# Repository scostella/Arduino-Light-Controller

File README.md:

# Arduino Light Controller

The **Arduino Light Controller** is a passive output board designed to provide simple, reliable **on/off control of up to 16 lighting channels** using an Arduino microcontroller. The board routes Arduino I/O pins directly to lighting outputs and includes optional onboard current‑limiting resistors for direct LED connection.

This controller is intended for use with the **Arduino CMRI Library** in conjunction with an associated CMRI‑compatible shield.

---

## Overview

The Arduino Light Controller connects Arduino digital or analog output pins to low‑current lighting loads. Each output is strictly **on or off**—there is no dimming, PWM, or active drive circuitry on the board.

The design emphasizes:

- Electrical simplicity  
- Clear signal routing  
- Safe use within Arduino current limits  
- Compatibility with Arduino CMRI‑based control systems  

---

## Key Characteristics

- 16 independent lighting output channels  
- On/off control only  
- Arduino 5 V I/O pins directly power outputs  
- Optional onboard 1 kΩ series resistors for LEDs  
- Jumper‑selectable resistor bypass per channel  
- Designed for Arduino CMRI Library usage with a compatible shield  
- Passive design (no relays, MOSFETs, or drivers)  

---

## Assembled Board

The image above shows the assembled Arduino Light Controller PCB with all connectors and headers populated.

---

## Board Layout and Function

### Top of Board – Arduino Control Headers

At the **top edge of the board** is a row of **four 4‑pin headers**.

- These headers connect directly to **Arduino digital or analog output pins**
- Together they control **16 lighting channels**
- Each pin corresponds to **one lighting output**
- Typically connected via ribbon cable or directly from a CMRI‑compatible shield

Each Arduino output pin switches one lighting channel on or off.

---

### Middle of Board – Resistor Bypass Headers

In the **center of the board** are **two rows of eight 2‑pin headers**.

- Each header corresponds to **one lighting channel**
- These headers allow bypassing the onboard **1 kΩ series resistor**

#### Built‑In Current Limiting

- Each output includes a **1 kΩ resistor** in series
- This allows **LEDs to be connected directly** to the board without external resistors

#### Resistor Bypass

- If the connected lighting already includes its own resistance:
  - A jumper may be installed on the corresponding 2‑pin header
  - This **bypasses the onboard 1 kΩ resistor**

This provides flexibility for:
- Pre‑resisted LEDs  
- Commercial lighting assemblies  
- External resistor networks  

---

### Bottom of Board – Light Output Headers

At the **bottom edge of the board** is a row of **sixteen 2‑pin headers**.

- Each header corresponds directly to one Arduino control pin
- Used to connect the lighting loads

#### Output Polarity

- **Top pin:** Positive (Arduino output)  
- **Bottom pin:** Ground / Negative  

⚠️ **Important:**  
Lighting loads are powered **directly from Arduino I/O pins**.  
Do not exceed Arduino per‑pin or total I/O current limits.

---

### Power Bus and Daisy Chaining

As with other modules in this series, the board includes:

- One **3‑pin header in the top‑left corner**
- One **3‑pin header in the top‑right corner**

These headers provide a shared **power bus** for:

- **12 V**
- **5 V**
- **Ground**

#### Power Bus Notes

- Allows **daisy chaining multiple modules**
- Maximum combined current across the bus: **3 A**
- Intended for system power distribution only  
  (lighting outputs are not powered from this bus)

---

## Electrical Characteristics and Limitations

- Control type: **On/Off only**
- No dimming or PWM
- No active output drivers
- No isolation from Arduino I/O
- Outputs driven directly from Arduino pins
- Designed for low‑current lighting only

⚠️ **Exceeding Arduino current limits may damage the microcontroller.**

---

## Intended Use

This board is well suited for:

- Arduino CMRI‑based layouts
- Model railroad lighting and structures
- Control panels and indicators
- Building and interior lighting
- Any application requiring simple, predictable lighting control

---

## Limited Liability and Disclaimer

This project is provided as an **open‑source hardware design** and is offered **as‑is**, without warranty of any kind.

By using this design, documentation, or any assembled hardware provided by the author, you agree to the following:

- You assume **all responsibility** for proper electrical design, wiring, installation, and use
- The author makes **no guarantees** regarding suitability for any specific application
- The author shall not be held liable for:
  - Damage to equipment
  - Electrical failures
  - Personal injury
  - Property damage
  - Losses resulting from improper use, installation, or modification

Use of this project or any associated hardware constitutes acceptance of these terms.

---

## Availability and Purchase

Fully **assembled and tested** Arduino Light Controller boards are available.

- **Price:** $35 USD per board  
- **Shipping:** Additional, based on destination  
- **Contact:**  
  📧 scostella@seancostella.com  

Please contact the author for current availability, lead times, and shipping details.

---

## Reference Projects

This project integrates with the Arduino CMRI ecosystem. The following projects provide related hardware, firmware, and configuration support:

- **Arduino Mega CMRI WiFi**  
  Arduino sketch for Mega 2560 to operate as CMRI Node with an ESP8266-ESP01 providing WiFi connectivity.
  https://github.com/scostella/Arduino_Mega_CMRI_WiFi

- **ESP8266 WiFi Setup Utility**  
  ESP sketch to program the ESP8266-ESP01 to work with the Arduino Mega 2560 and connection configuration for your WiFi network.
  https://github.com/scostella/ESP8266WiFiSetup
  
- **KiCad Custom Library**  
  Library containing all project parts in all designs.
  https://github.com/scostella/KiCadLibrary

- **Arduino Mega CMRI WiFi Shield**  
  KiCad design for a shield for the Arduino Mega 2560 facilitating easy integration with the ESP8266-ESP01 and the CMRI modules listed below.
  https://github.com/scostella/Arduino_Mega_CMRI_WiFi_Shield

- **Arduino Accessory Controller**  
  KiCad design for a board to control accessories up to 1 amp.
  https://github.com/scostella/Arduino-Accessory-Controller

- **Arduino IR Sensor Module - 8 Port**  
  KiCad design for a board to use TCRT5000 IR module to sense object presence which can also be used in the Arduino Mega CMRI WiFi module to group sensors to create virtual block detection.
  https://github.com/scostella/Arduino_IR_Sensor_Module_-_8_Port

- **Arduino Tortoise Controller with Feedback - 8 Port**  
  KiCad design for a board to control Circuitron Tortoise Slow Motion Switch machines and provide feedback on switch position either controlled internally by the voltage applied to the tortoise or an external signal.
  https://github.com/scostella/Arduino_Tortoise_Controller_with_Feedback_-_8_Port

- **Arduino Light Controller**  
  KiCad design for a board to control low amperage lighting and other loads (<10ma) using the Arduino's 5V source.
  https://github.com/scostella/Arduino-Light-Controller

These projects may be used together to form a complete CMRI‑controlled lighting and I/O system.

---

## Repository Contents

```text
/
├── Arduino Light Controller.kicad_pcb        # KiCad PCB Layout
├── Arduino Light Controller.kicad_prl        # KiCad Project Settings
├── Arduino Light Controller.kicad_pro        # KiCad Project
├── Arduino Light Controller.kicad_sch        # KiCad Schematics
├── PowerLED.kicad_sch                        # KiCad Power and LED module
├── ResistorNet.kicad_sch                     # KiCad Light Control Resistor and Bypass module
├── Arduino Light Controller.jpg              # Board Rendering
└── README.md

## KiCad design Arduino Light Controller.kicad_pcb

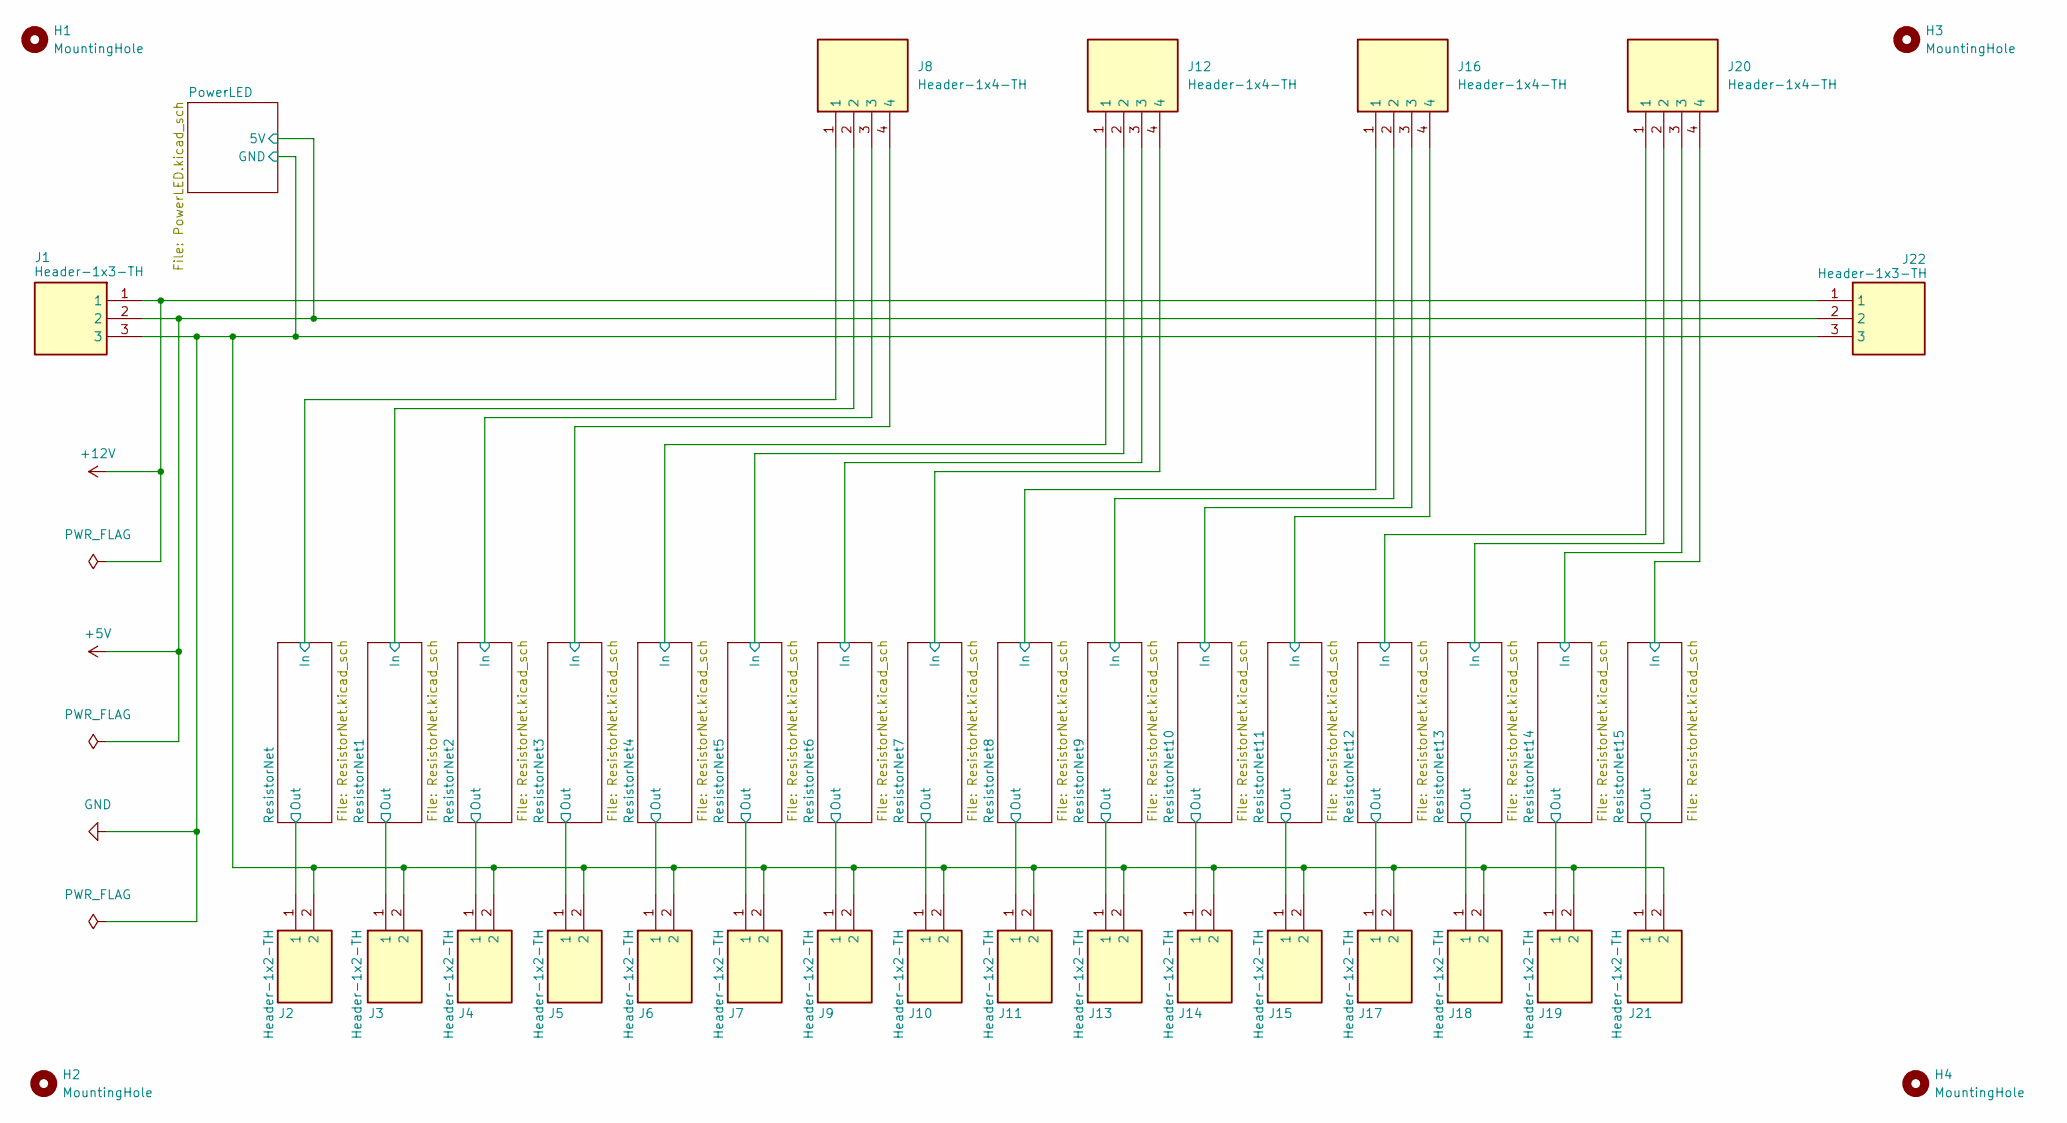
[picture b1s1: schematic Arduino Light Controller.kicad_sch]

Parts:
H1, H2, H3, H4: MountingHole; MountingHole_3.2mm_M3_ISO7380
J1, J22: Header-1x3-TH; 710-61300311121; Mouser Part Number 710-61300311121
J2, J3, J4, J5, J6, J7, J9, J10, J11, J13, J14, J15, J17, J18, J19, J21: Header-1x2-TH; 710-61300211121; Mouser Part Number 710-61300211121
J8, J12, J16, J20: Header-1x4-TH; 710-61300411121; Mouser Part Number 710-61300411121

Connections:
+5V: J1.2, J22.2; also elsewhere on the board
+12V: J1.1, J22.1
/ResistorNet1/In: J8.2; also elsewhere on the board
/ResistorNet1/Out: J3.1; also elsewhere on the board
/ResistorNet2/In: J8.3; also elsewhere on the board
/ResistorNet2/Out: J4.1; also elsewhere on the board
/ResistorNet3/In: J8.4; also elsewhere on the board
/ResistorNet3/Out: J5.1; also elsewhere on the board
/ResistorNet4/In: J12.1; also elsewhere on the board
/ResistorNet4/Out: J6.1; also elsewhere on the board
/ResistorNet5/In: J12.2; also elsewhere on the board
/ResistorNet5/Out: J7.1; also elsewhere on the board
/ResistorNet6/In: J12.3; also elsewhere on the board
/ResistorNet6/Out: J9.1; also elsewhere on the board
/ResistorNet7/In: J12.4; also elsewhere on the board
/ResistorNet7/Out: J10.1; also elsewhere on the board
/ResistorNet8/In: J16.1; also elsewhere on the board
/ResistorNet8/Out: J11.1; also elsewhere on the board
/ResistorNet9/In: J16.2; also elsewhere on the board
/ResistorNet9/Out: J13.1; also elsewhere on the board
/ResistorNet10/In: J16.3; also elsewhere on the board
/ResistorNet10/Out: J14.1; also elsewhere on the board
/ResistorNet11/In: J16.4; also elsewhere on the board
/ResistorNet11/Out: J15.1; also elsewhere on the board
/ResistorNet12/In: J20.1; also elsewhere on the board
/ResistorNet12/Out: J17.1; also elsewhere on the board
/ResistorNet13/In: J20.2; also elsewhere on the board
/ResistorNet13/Out: J18.1; also elsewhere on the board
/ResistorNet14/In: J20.3; also elsewhere on the board
/ResistorNet14/Out: J19.1; also elsewhere on the board
/ResistorNet15/In: J20.4; also elsewhere on the board
/ResistorNet15/Out: J21.1; also elsewhere on the board
/ResistorNet/In: J8.1; also elsewhere on the board
/ResistorNet/Out: J2.1; also elsewhere on the board
GND: J1.3, J2.2, J3.2, J4.2, J5.2, J6.2, J7.2, J9.2, J10.2, J11.2, J13.2, J14.2, J15.2, J17.2, J18.2, J19.2, J21.2, J22.3; also elsewhere on the board

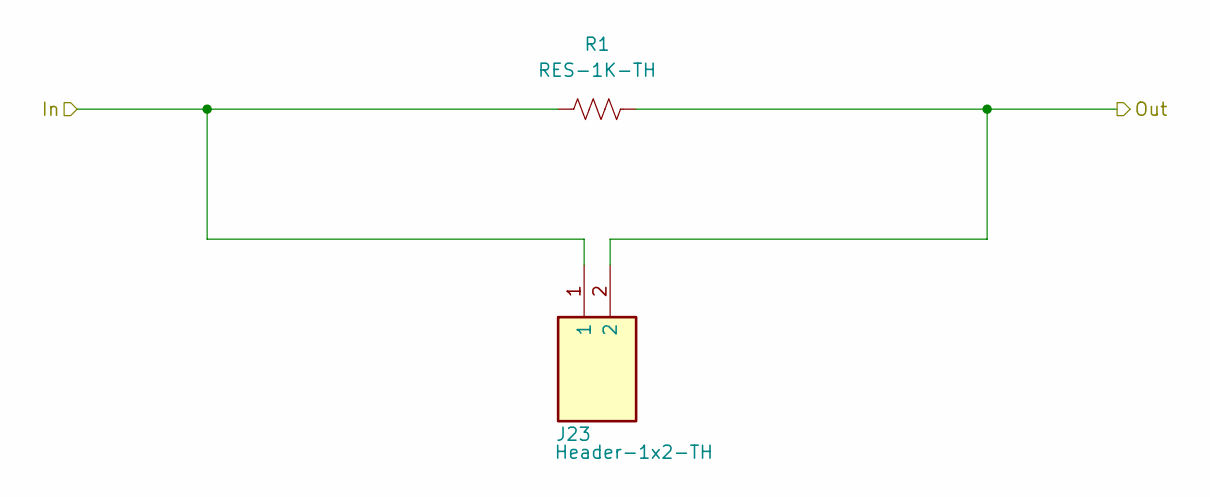
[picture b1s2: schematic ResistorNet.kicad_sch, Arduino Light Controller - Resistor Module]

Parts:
J23: Header-1x2-TH; 710-61300211121; Mouser Part Number 710-61300211121
R1: RES-1K-TH; R_Axial_DIN0204_L3.6mm_D1.6mm_P7.62mm_Horizontal; Mouser Part Number N/A

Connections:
/ResistorNet/In: J23.1, R1.1; also elsewhere on the board
/ResistorNet/Out: J23.2, R1.2; also elsewhere on the board

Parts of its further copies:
J24, J25, J26, J27, J28, J29, J30, J31, J32, J33, J34, J35, J36, J37, J38: Header-1x2-TH; 710-61300211121; Mouser Part Number 710-61300211121
R2, R3, R4, R5, R6, R7, R8, R9, R10, R11, R12, R13, R14, R15, R16: RES-1K-TH; R_Axial_DIN0204_L3.6mm_D1.6mm_P7.62mm_Horizontal; Mouser Part Number N/A

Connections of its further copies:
/ResistorNet1/In: J24.1, R2.1; also elsewhere on the board
/ResistorNet1/Out: J24.2, R2.2; also elsewhere on the board
/ResistorNet2/In: J25.1, R3.1; also elsewhere on the board
/ResistorNet2/Out: J25.2, R3.2; also elsewhere on the board
/ResistorNet3/In: J26.1, R4.1; also elsewhere on the board
/ResistorNet3/Out: J26.2, R4.2; also elsewhere on the board
/ResistorNet4/In: J27.1, R5.1; also elsewhere on the board
/ResistorNet4/Out: J27.2, R5.2; also elsewhere on the board
/ResistorNet5/In: J28.1, R6.1; also elsewhere on the board
/ResistorNet5/Out: J28.2, R6.2; also elsewhere on the board
/ResistorNet6/In: J29.1, R7.1; also elsewhere on the board
/ResistorNet6/Out: J29.2, R7.2; also elsewhere on the board
/ResistorNet7/In: J30.1, R8.1; also elsewhere on the board
/ResistorNet7/Out: J30.2, R8.2; also elsewhere on the board
/ResistorNet8/In: J31.1, R9.1; also elsewhere on the board
/ResistorNet8/Out: J31.2, R9.2; also elsewhere on the board
/ResistorNet9/In: J32.1, R10.1; also elsewhere on the board
/ResistorNet9/Out: J32.2, R10.2; also elsewhere on the board
/ResistorNet10/In: J33.1, R11.1; also elsewhere on the board
/ResistorNet10/Out: J33.2, R11.2; also elsewhere on the board
/ResistorNet11/In: J34.1, R12.1; also elsewhere on the board
/ResistorNet11/Out: J34.2, R12.2; also elsewhere on the board
/ResistorNet12/In: J35.1, R13.1; also elsewhere on the board
/ResistorNet12/Out: J35.2, R13.2; also elsewhere on the board
/ResistorNet13/In: J36.1, R14.1; also elsewhere on the board
/ResistorNet13/Out: J36.2, R14.2; also elsewhere on the board
/ResistorNet14/In: J37.1, R15.1; also elsewhere on the board
/ResistorNet14/Out: J37.2, R15.2; also elsewhere on the board
/ResistorNet15/In: J38.1, R16.1; also elsewhere on the board
/ResistorNet15/Out: J38.2, R16.2; also elsewhere on the board

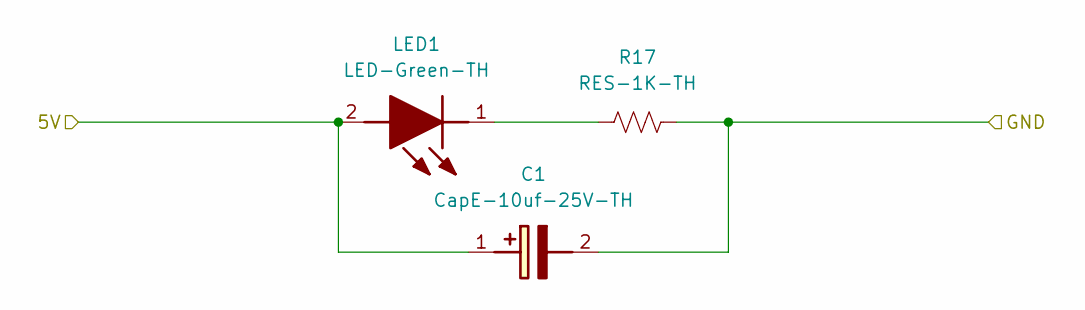
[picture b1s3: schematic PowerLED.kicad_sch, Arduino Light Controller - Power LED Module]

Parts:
C1: CapE-10uf-25V-TH; 710-860010472002; Mouser Part Number 710-860010472002
LED1: LED-Green-TH; 604-WP7113GD; Mouser Part Number 604-WP7113GD
R17: RES-1K-TH; R_Axial_DIN0204_L3.6mm_D1.6mm_P7.62mm_Horizontal; Mouser Part Number N/A

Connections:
+5V: C1.1 (+), LED1.2 (A); also elsewhere on the board
GND: C1.2 (-), R17.2; also elsewhere on the board
unnamed: LED1.1 (K), R17.1

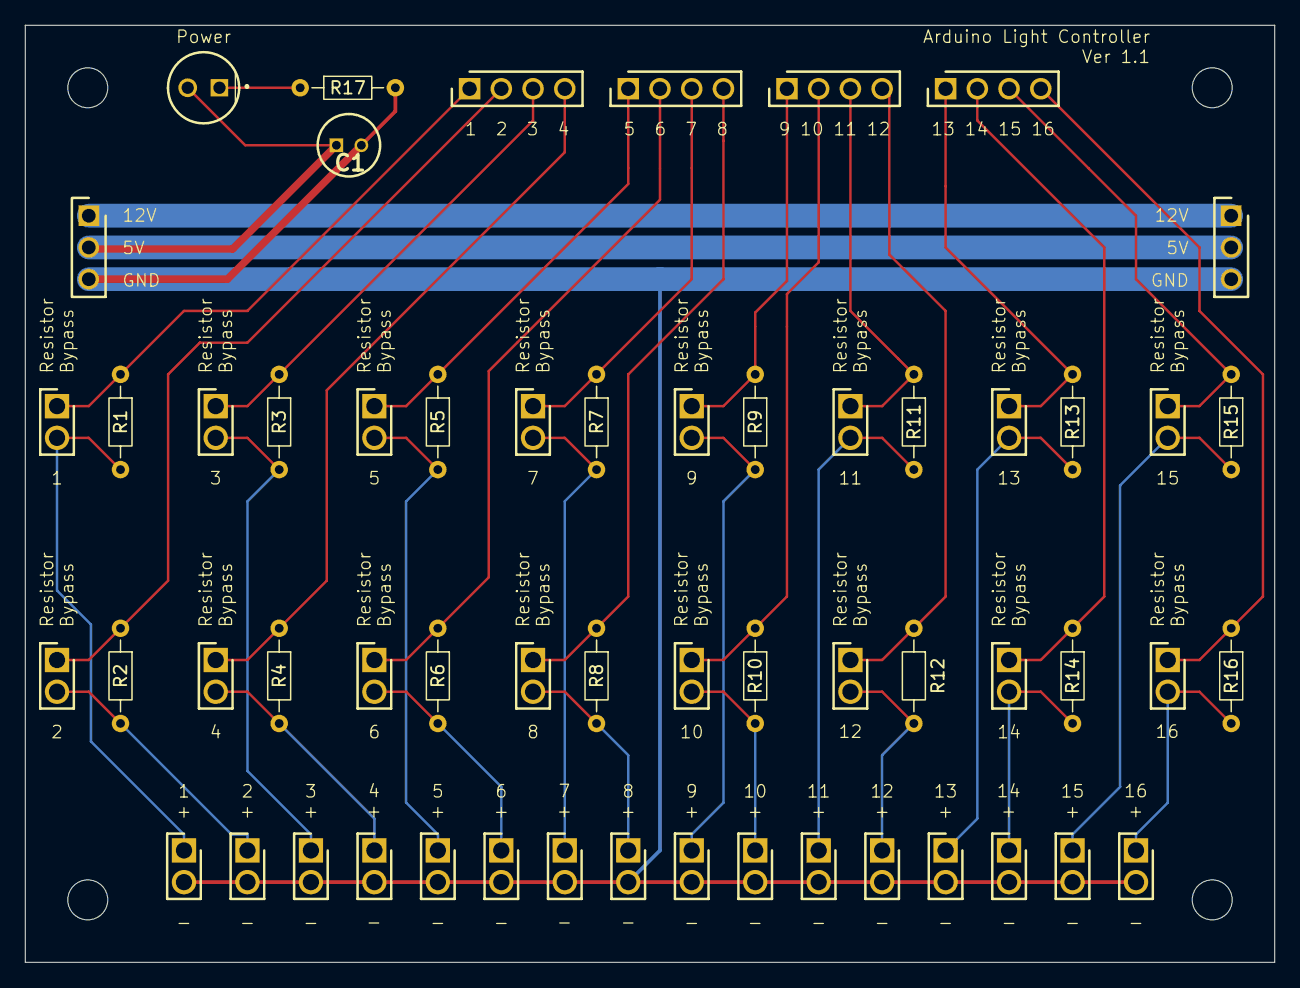
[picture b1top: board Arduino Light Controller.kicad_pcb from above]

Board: 2 copper layers, 100.0 x 75.0 mm, 61 parts (0 on the bottom side), 36 nets.

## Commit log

2025-12-31 Original project created and used.
2025-12-31 New design to align with other boards and support power bus.
2025-12-31 Created Gerber Export and BOM.
2026-01-24 Created the PowerLED subschematic and replaced the 100nF capacitor with a 10uF capacitor, added .gitignore file to ignore backups and lock file.
2026-01-25 Updated re-annotated the schematics, created new PCB based on standards and updated components.
2026-01-30 Updated components to the custom library and applied additional standards.
2026-01-30 Added Resistor Bypass label to jumper pins.
2026-01-30 Updated sheets with title, version, and date. Corrected issue with resistor placement and connection on PowerLED module.
2026-01-31 Missed updating PowerLED module with components from the custom library.
2026-02-14 Added picture of assembled v1.1 board.
2026-02-14 Updated PCB with new 3d models as well as exported image for use with repo README.md.
2026-02-14 Created README.md for the project.
2026-02-14 Working on image display.
2026-02-14 Updated README.md with project structure.
2026-02-14 Updated README.md for purchase and limited liability.
2026-02-15 Updated README.md with all reference projects.
2026-02-15 Adjusted verbiage on Reference Projects.
2026-02-15 Added KiCad Custom Library to project references.
